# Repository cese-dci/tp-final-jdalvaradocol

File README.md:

## Trabajo práctico final de la asignatura DCI ##
Este repositorio contiene el trabajo práctico final para la asignatura de Diseño de Circuitos Impresos de la carrera de posgrado de FIUBA.

* Autor: Jose David Alvarado Moreno
* Título corto del trabajo:  Sheild EK-TM4C1294XL
* Descripción:  Sheild EK-TM4C1294XL

## Licencia de este trabajo ##
MIT License

## Estructura del TP FINAL ##

Se propone y se pide utilizar la siguiente estructura.

* doc: Toda la información sobre el circuito, principalmente de autoría o procesamiento propio. Por ejemplo:
  * Notas de ingeniería propias.
  * Notas de aplicación propias.
  * Estudios previos, estado del arte, resumen de las investigaciones.
  * Notas con cálculos.
  * Dibujos adicionales.
  * Fotos de los prototipos.
  * Presupuestos, cotizaciones.
* info: Toda la iformación recolectada, principalmente de terceros, como por ejemplo:
  * Hojas de datos.
  * Notas de aplicación.
  * Info de productos comerciales.
  * Info en internet.
* pcb: Archivos de diseño esquemático y pcb.

Dependiendo la magnitud del proyecto, tendremos más o menos información en estos directorios. 
Revisar los README.md en cada directorio para conocer las pautas de cada uno para este TP.

NOTA: El alumno puede y debe borrar de este archivo todo lo que considere necesario, por ejemplo las aclaraciones del docente y esta misma nota.

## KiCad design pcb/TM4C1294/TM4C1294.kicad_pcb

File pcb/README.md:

## Archivos Kicad ##

* Archivos de proyecto.
* Esquemático.
* PCB.
* Modelos  3D.
* Bibliotecas de símbolos y huellas externas (si son necesarios).

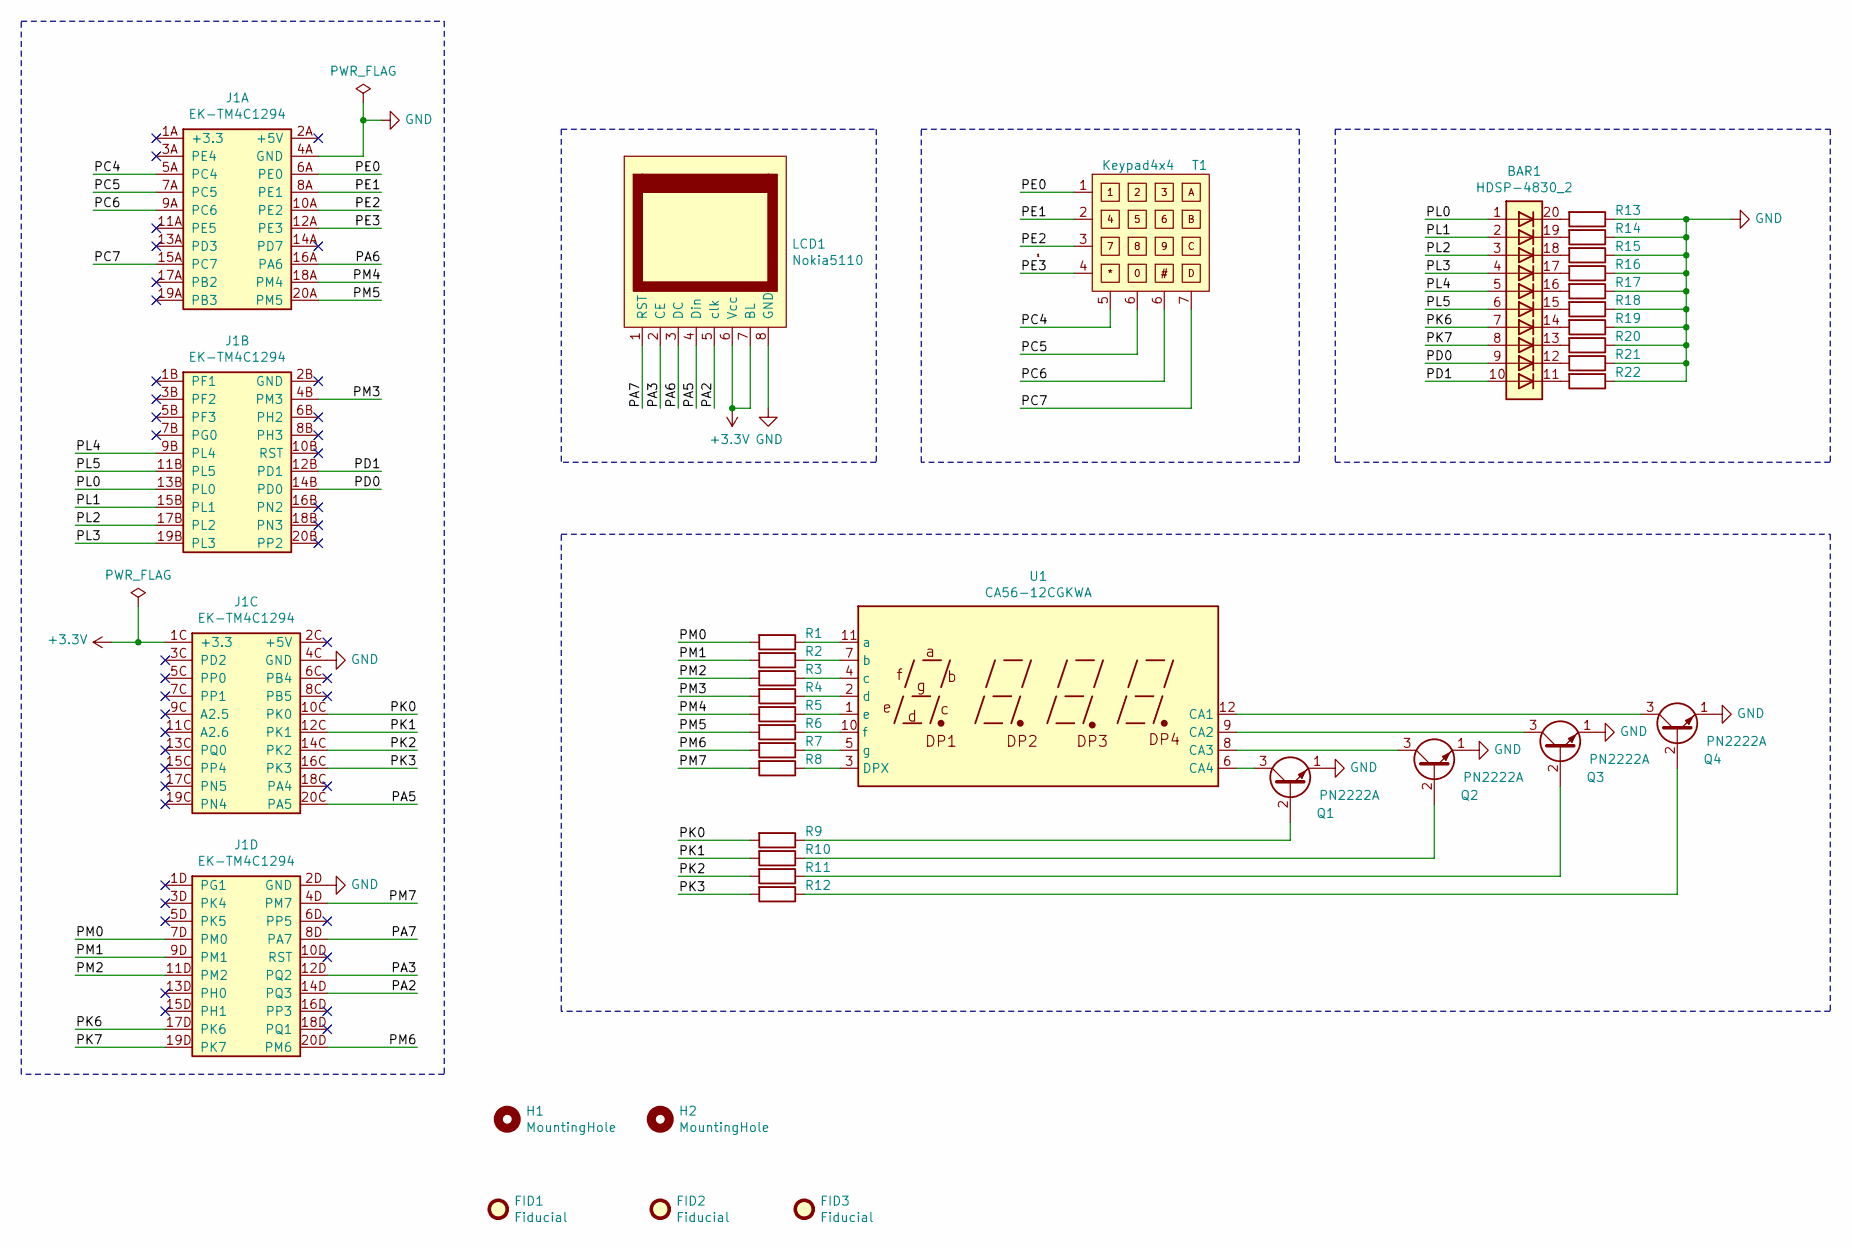
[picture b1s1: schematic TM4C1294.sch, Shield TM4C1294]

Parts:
BAR1: HDSP-4830_2; HDSP-4830
FID1, FID2, FID3: Fiducial; Fiducial_0.5mm_Mask1.5mm
H1, H2: MountingHole; MountingHole_3mm
J1: EK-TM4C1294
LCD1: Nokia5110
Q1, Q2, Q3, Q4: PN2222A; TO-92_Inline_Wide
R1, R2, R3, R4, R5, R6, R7, R8, R9, R10, R11, R12, R13, R14, R15, R16, R17, R18, R19, R20, R21, R22: R; R_Axial_DIN0207_L6.3mm_D2.5mm_P7.62mm_Horizontal
T1: Keypad4x4; Keypad
U1: CA56-12CGKWA

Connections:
+3V3: J1.1C (+3.3), LCD1.6 (Vcc), LCD1.7 (BL)
/PA2: J1.14D (PQ3), LCD1.5 (clk)
/PA3: J1.12D (PQ2), LCD1.2 (CE)
/PA5: J1.20C (PA5), LCD1.4 (Din)
/PA6: J1.16A (PA6), LCD1.3 (DC)
/PA7: J1.8D (PA7), LCD1.1 (RST)
/PC4: J1.5A (PC4), T1.5
/PC7: J1.15A (PC7), T1.7
/PD0: BAR1.9 (A), J1.14B (PD0)
/PD1: BAR1.10 (A), J1.12B (PD1)
/PE0: J1.6A (PE0), T1.1
/PE1: J1.8A (PE1), T1.2
/PE2: J1.10A (PE2), T1.3
/PE3: J1.12A (PE3), T1.4
/PK0: J1.10C (PK0), R9.2
/PK1: J1.12C (PK1), R10.2
/PK2: J1.14C (PK2), R11.2
/PK3: J1.16C (PK3), R12.2
/PK6: BAR1.7 (A), J1.17D (PK6)
/PK7: BAR1.8 (A), J1.19D (PK7)
/PL0: BAR1.1 (A), J1.13B (PL0)
/PL1: BAR1.2 (A), J1.15B (PL1)
/PL2: BAR1.3 (A), J1.17B (PL2)
/PL3: BAR1.4 (A), J1.19B (PL3)
/PL4: BAR1.5 (A), J1.9B (PL4)
/PL5: BAR1.6 (A), J1.11B (PL5)
/PM0: J1.7D (PM0), R1.2
/PM1: J1.9D (PM1), R2.2
/PM2: J1.11D (PM2), R3.2
/PM3: J1.4B (PM3), R4.2
/PM4: J1.18A (PM4), R5.2
/PM5: J1.20A (PM5), R6.2
/PM6: J1.20D (PM6), R7.2
/PM7: J1.4D (PM7), R8.2
GND: J1.2D (GND), J1.4A (GND), J1.4C (GND), LCD1.8 (GND), Q1.1 (E), Q2.1 (E), Q3.1 (E), Q4.1 (E), R13.1, R14.1, R15.1, R16.1, R17.1, R18.1, R19.1, R20.1, R21.1, R22.1
unnamed: BAR1.11 (K), R22.2
unnamed: BAR1.12 (K), R21.2
unnamed: BAR1.13 (K), R20.2
unnamed: BAR1.14 (K), R19.2
unnamed: BAR1.15 (K), R18.2
unnamed: BAR1.16 (K), R17.2
unnamed: BAR1.17 (K), R16.2
unnamed: BAR1.18 (K), R15.2
unnamed: BAR1.19 (K), R14.2
unnamed: BAR1.20 (K), R13.2
unnamed: Q1.2 (B), R9.1
unnamed: Q1.3 (C), U1.6 (CA4)
unnamed: Q2.2 (B), R10.1
unnamed: Q2.3 (C), U1.8 (CA3)
unnamed: Q3.2 (B), R11.1
unnamed: Q3.3 (C), U1.9 (CA2)
unnamed: Q4.2 (B), R12.1
unnamed: Q4.3 (C), U1.12 (CA1)
unnamed: R1.1, U1.11 (a)
unnamed: R2.1, U1.7 (b)
unnamed: R3.1, U1.4 (c)
unnamed: R4.1, U1.2 (d)
unnamed: R5.1, U1.1 (e)
unnamed: R6.1, U1.10 (f)
unnamed: R7.1, U1.5 (g)
unnamed: R8.1, U1.3 (DPX)

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
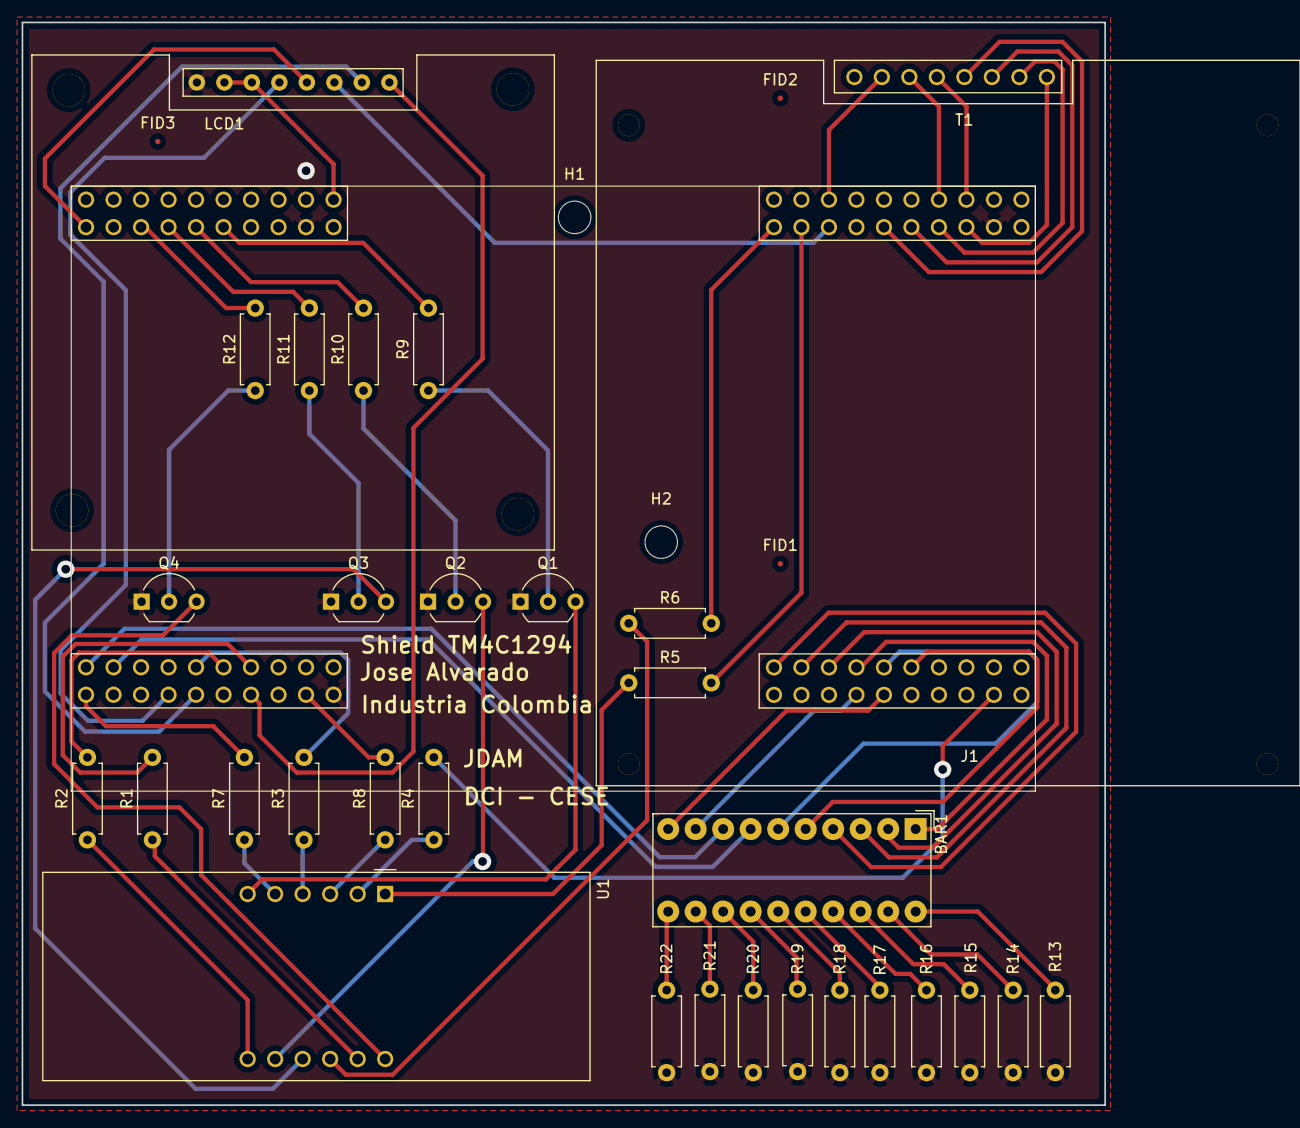
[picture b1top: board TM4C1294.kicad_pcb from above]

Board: 2 copper layers, 100.0 x 100.0 mm, 36 parts (0 on the bottom side), 62 nets.

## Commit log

2021-09-23 Version 1.0
2021-09-23 Create LICENSE
2021-10-14 PCB V 2.0
2021-10-15 PCB v1.0
2021-10-15 Readme Kicad

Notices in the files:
pcb/TM4C1294/TM4C1294.kicad_pcb:
Licencia CC BY 4.0
